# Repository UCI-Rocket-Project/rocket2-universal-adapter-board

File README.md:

## rocket2's universal adapter board for sensors
Converts a suite of sensors inputs into a female DSUB adapter  
  
More information on design: [Click Here](https://uci-rocket-project.github.io/rocket2-overview/standardized_connectors/)  

## CAD

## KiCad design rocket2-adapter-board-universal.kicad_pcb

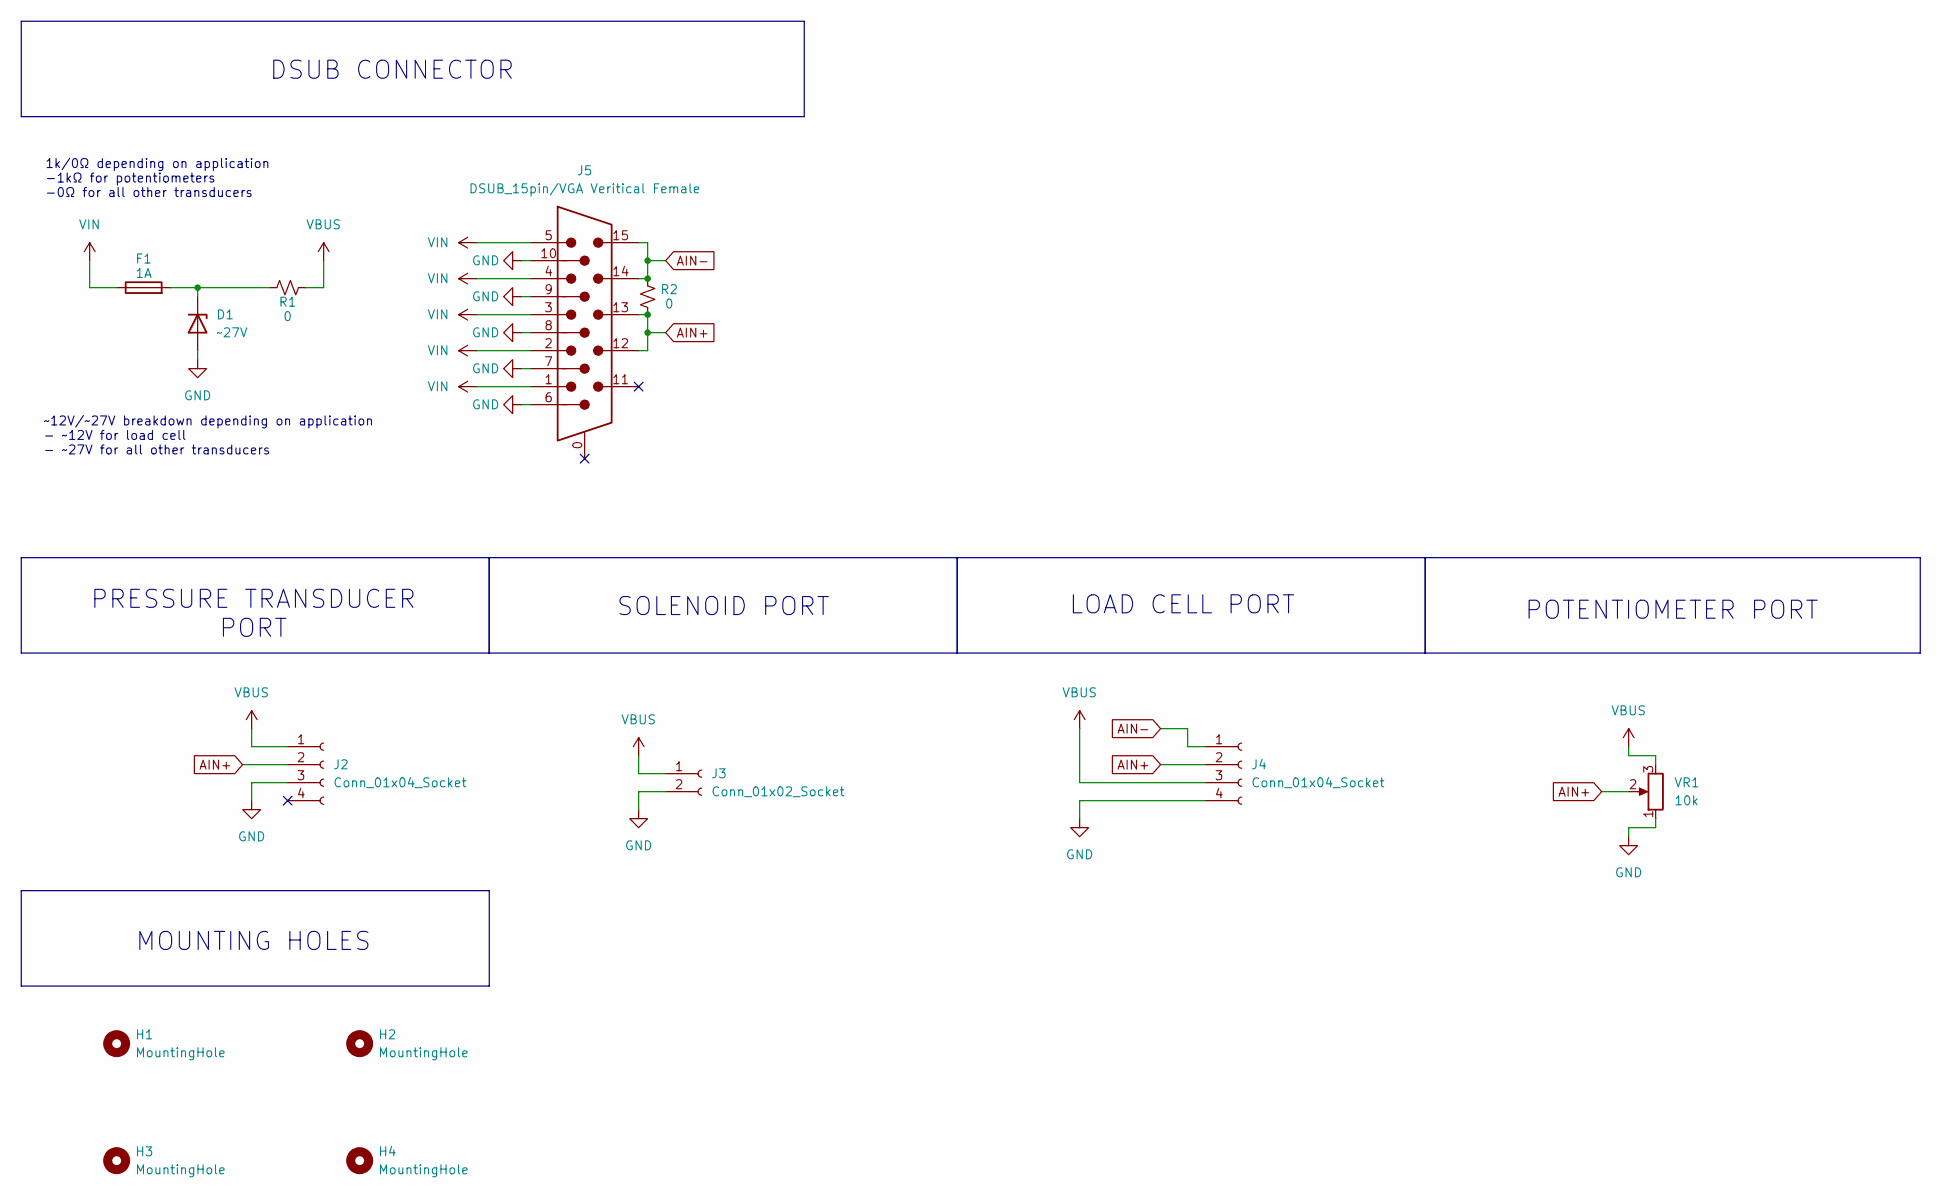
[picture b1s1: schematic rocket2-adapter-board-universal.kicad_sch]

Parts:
D1: ~27V; D_SOD-123
F1: 1A; Fuseholder_Blade_Mini_Keystone_3568
H1: MountingHole; MountingHole_3.2mm_M3_DIN965_Pad
H2, H3, H4: MountingHole; MountingHole_3.2mm_M3_ISO7380_Pad
J2: Conn_01x04_Socket; Pad_Socket 9.4mm_MiniDIN
J3: Conn_01x02_Socket; Pad_Socket 16AWG_Solenoid_Wires
J4: Conn_01x04_Socket; PinHeader_1x04_P2.54mm_Vertical
J5: DSUB_15pin/VGA Veritical Female; Connector_VGA_Vertical
R1, R2: 0; R_0603_1608Metric; MPN 0603WAJ0000T5E
VR1: 10k; Potentiometer P160KNPD4FC20B10K; MPN P160KNPD-4FC20B10K

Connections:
AIN+: J2.2, J4.2, J5.12, J5.13, R2.2, VR1.2
AIN-: J4.1, J5.14, J5.15, R2.1
GND: D1.2 (A), J2.3, J3.2, J4.4, J5.6, J5.7, J5.8, J5.9, J5.10, VR1.1
unnamed: D1.1 (K), F1.2, R1.2
VBUS: J2.1, J3.1, J4.3, R1.1, VR1.3
VIN: F1.1, J5.1, J5.2, J5.3, J5.4, J5.5

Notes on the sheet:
PRESSURE TRANSDUCER PORT
POTENTIOMETER PORT
DSUB CONNECTOR
SOLENOID PORT
MOUNTING HOLES
~12V/~27V breakdown depending on application - ~12V for load cell - ~27V for all other transducers
LOAD CELL PORT
1k/0Ω depending on application -1kΩ for potentiometers -0Ω for all other transducers

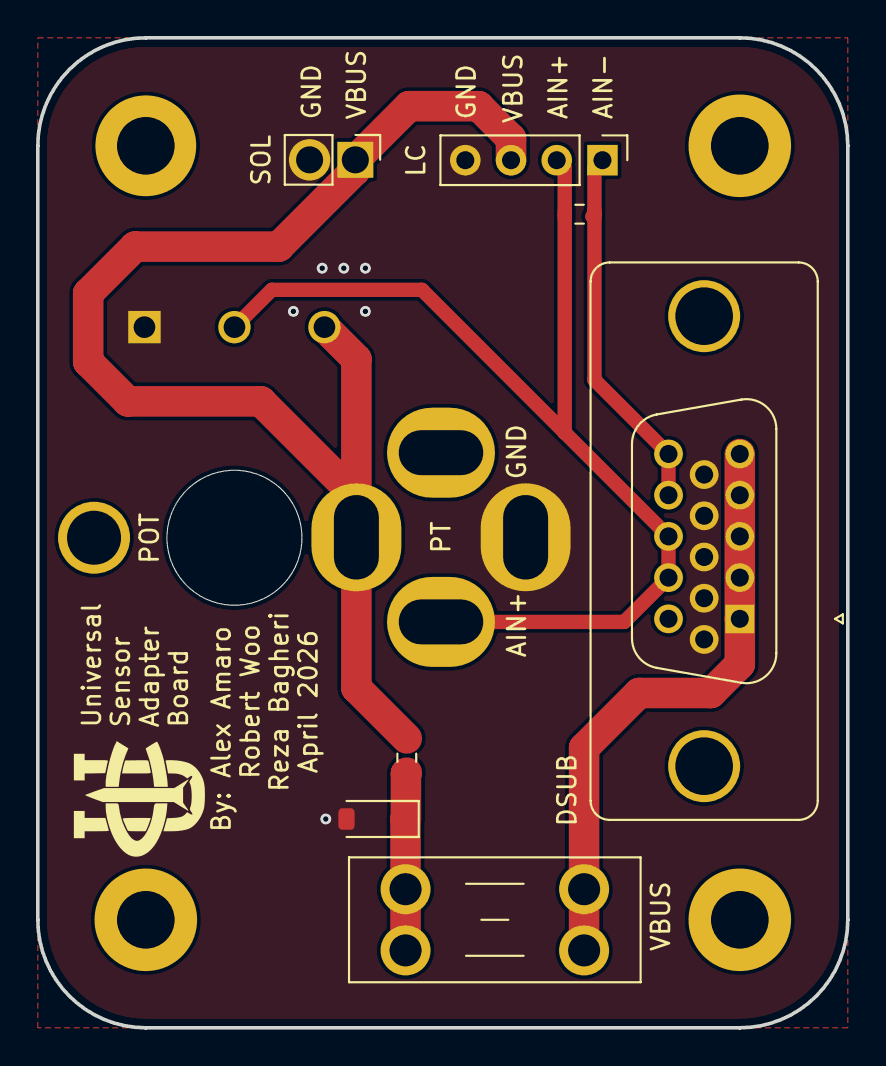
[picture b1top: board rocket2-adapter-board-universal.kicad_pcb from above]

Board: 2 copper layers, 45.0 x 55.0 mm, 13 parts (1 on the bottom side), 6 nets.

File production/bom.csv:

Designator,Footprint,Quantity,Value,LCSC Part #
D1,D_SOD-123,1,~27V,
F1,Fuseholder_Blade_Mini_Keystone_3568,1,1A,
J2,Pad_Socket 9.4mm_MiniDIN,1,Conn_01x04_Socket,
J3,Pad_Socket 16AWG_Solenoid_Wires,1,Conn_01x02_Socket,
J4,PinHeader_1x04_P2.54mm_Vertical,1,Conn_01x04_Socket,
J5,Connector_VGA_Vertical,1,DSUB_15pin/VGA Veritical  Female,
"R1, R2",0603,2,0,0603WAJ0000T5E
VR1,Potentiometer P160KNPD4FC20B10K,1,10k,P160KNPD-4FC20B10K

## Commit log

2026-03-26 Prelim Schematic & Layout
    DSUB and GX Connector Only
2026-03-26 Quick Fix: Unconnected Pad
    Added routing to a disconnected pad on pulldown pins
2026-04-02 BOM Generation Available + Standard KiCad Library
    Added webpages for JLCPCB pre-assembly BOM. Added new standardized KiCAD library.
2026-04-02 Updated R2 Purchase Link
2026-04-02 Corrected R2 Link
2026-04-03 Layout Update
2026-04-03 Quick Silkscreen Fix
2026-04-03 Layout Update 2 + DSUB & Footprint Fixes
2026-04-03 Layout Return Paths Fix
    Streamlined GND return paths
2026-04-05 Layout Update 3 + Schematic Links & DSUB Update
    Added R2 to bridge AIN+ and AIN-
2026-04-06 Layout Update 4: NC pins, PT and Solenoid pad fixes
2026-04-07 Layout Update 5: Part spacing, Footprints, and Models
2026-04-07 PT Footprint Update
2026-04-08 PT Footprint Update 2
    Adjusted thickness to 1mm
2026-04-08 Final PT Footprint Update
    Added an extra 1mm to all tolerances
2026-04-08 Layout Update 6: Updated PT footprint, Silkscreen labels, M3s
2026-04-08 Ready for purchasing
2026-04-08 Repositioned things so it would fit better
2026-04-18 Updated for order
2026-05-05 Fixed resistor value/comments for POTs config
2026-05-05 Update README with project details and CAD image
    Added project overview and CAD image to README.
